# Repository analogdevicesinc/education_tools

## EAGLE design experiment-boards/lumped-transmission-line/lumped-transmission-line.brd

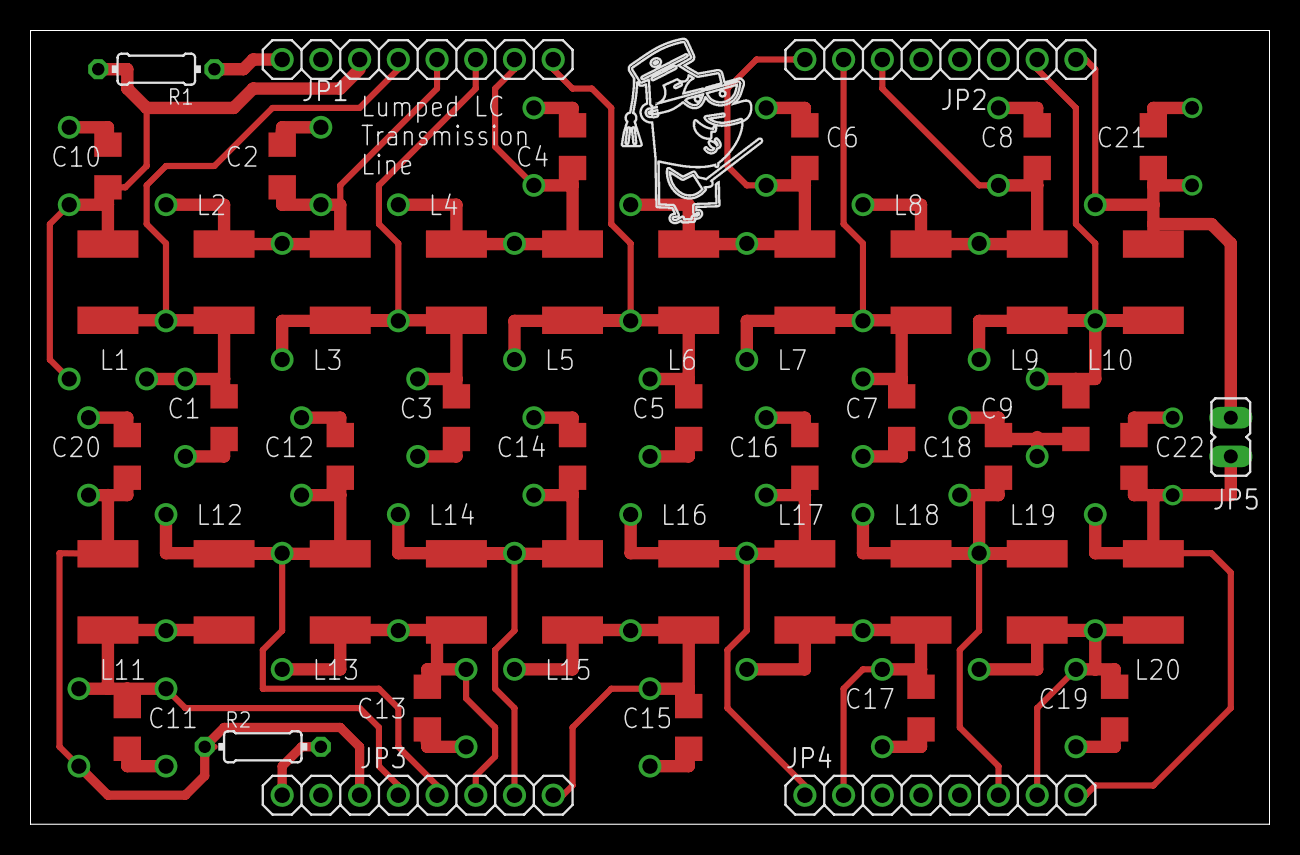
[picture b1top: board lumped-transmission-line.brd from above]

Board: 2 copper layers, 81.3 x 52.1 mm, 50 parts (0 on the bottom side), 25 nets.

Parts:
C1, C2, C3, C4, C5, C6, C7, C8, C9, C10, C11, C12, C13, C14, C15, C16, C17, C18, C19, C20, C21, C22: C1206
JP1, JP2, JP3, JP4: 1X08
JP5: JP1
L1, L2, L3, L4, L5, L6, L7, L8, L9, L10, L11, L12, L13, L14, L15, L16, L17, L18, L19, L20: L5650M
R1, R2: 50; 0204/7
U$1: PROFF

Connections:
GND: C1.2, C2.2, C3.2, C4.2, C5.2, C6.2, C7.2, C8.2, C9.2, C10.2, C11.2, C12.2, C13.2, C14.2, C15.2, C16.2, C17.2, C18.2, C19.2, C20.2, C21.2, C22.2, JP1.2, JP2.4, JP2.5, JP2.6, JP3.2, JP4.3, JP4.4, JP4.5
unnamed: C3.1, JP1.6, L3.2, L4.1
unnamed: C21.1, JP2.8, JP5.1, L10.2
unnamed: C22.1, JP4.8, JP5.2, L20.2
unnamed: C9.1, JP2.7, L9.2, L10.1
unnamed: C19.1, JP4.7, L19.2, L20.1
unnamed: JP1.1, R1.1
unnamed: C15.1, JP3.8, L15.2, L16.1
unnamed: C17.1, JP4.2, L17.2, L18.1
unnamed: C18.1, JP4.6, L18.2, L19.1
unnamed: JP3.1, R2.2
unnamed: C13.1, JP3.6, L13.2, L14.1
unnamed: C11.1, JP3.4, L11.2, L12.1
unnamed: C6.1, JP2.1, L6.2, L7.1
unnamed: C4.1, JP1.7, L4.2, L5.1
unnamed: C2.1, JP1.5, L2.2, L3.1
unnamed: C10.1, JP1.3, L1.1, R1.2
unnamed: C8.1, JP2.3, L8.2, L9.1
unnamed: C20.1, JP3.3, L11.1, R2.1
unnamed: C1.1, JP1.4, L1.2, L2.1
unnamed: C12.1, JP3.5, L12.2, L13.1
unnamed: C14.1, JP3.7, L14.2, L15.1
unnamed: C5.1, JP1.8, L5.2, L6.1
unnamed: C16.1, JP4.1, L16.2, L17.1
unnamed: C7.1, JP2.2, L7.2, L8.1

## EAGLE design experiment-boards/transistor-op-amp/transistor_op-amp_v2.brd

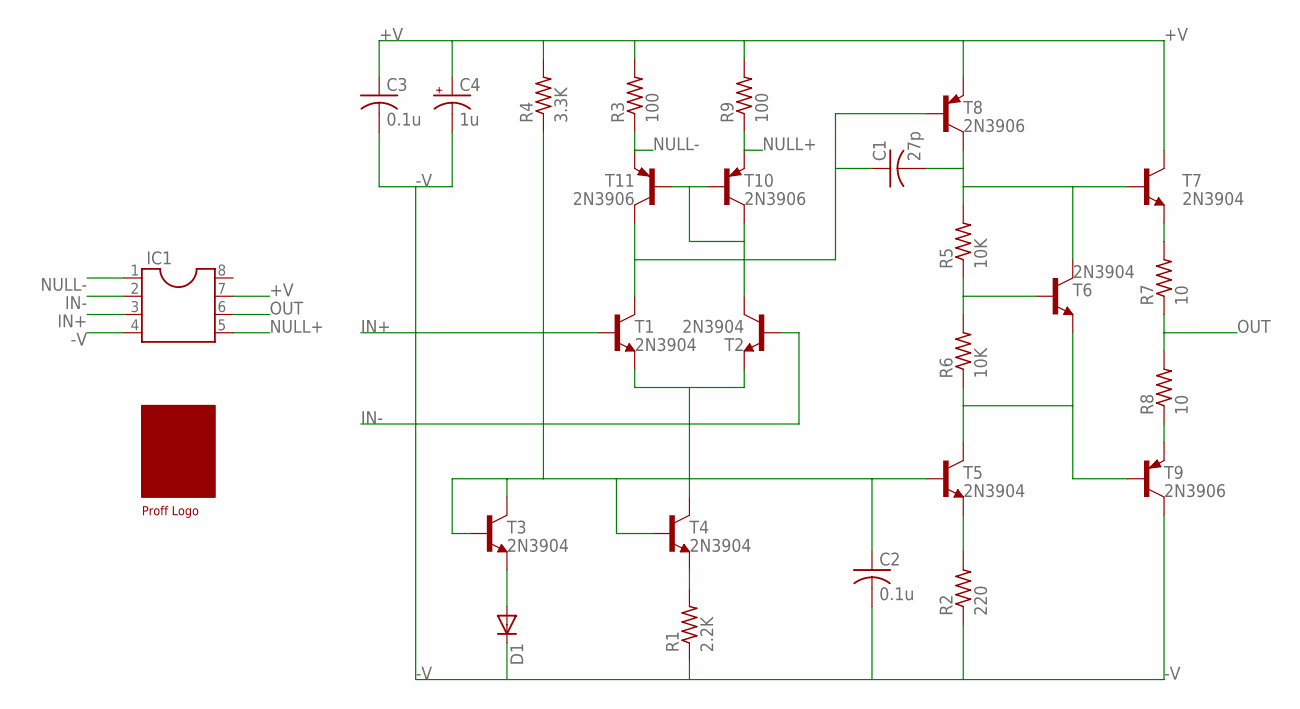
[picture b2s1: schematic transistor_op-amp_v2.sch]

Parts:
C1: 27p; C050-024X044
C2, C3: 0.1u; C050-024X044
C4: 1u; E2,5-5
D1: DIODE-D-7.5; D-7.5
IC1: DIL8S; SOCKET-08
R1: 2.2K; 0207/7
R2: 220; 0207/7
R3, R9: 100; 0207/7
R4: 3.3K; 0207/7
R5, R6: 10K; 0207/7
R7, R8: 10; 0207/7
T1, T2, T3, T4, T5, T6, T7: 2N3904; TO92
T8, T9, T10, T11: 2N3906; TO92
U$1: PROFF

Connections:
+V: C3.1, C4.+, IC1.7, R3.2, R4.2, R9.2, T7.1 (C), T8.3 (E)
-V: C2.2, C3.2, C4.-, D1.C, IC1.4, R1.1, R2.1, T9.1 (C)
IN+: IC1.3, T1.2 (B)
IN-: IC1.2, T2.2 (B)
unnamed: D1.A, T3.3 (E)
unnamed: C2.1, R4.1, T3.1 (C), T3.2 (B), T4.2 (B), T5.2 (B)
unnamed: R1.2, T4.3 (E)
unnamed: R2.2, T5.3 (E)
unnamed: T1.3 (E), T2.3 (E), T4.1 (C)
unnamed: R7.2, T7.3 (E)
unnamed: R6.1, T5.1 (C), T6.3 (E), T9.2 (B)
unnamed: R5.1, R6.2, T6.2 (B)
unnamed: C1.2, R5.2, T6.1 (C), T7.2 (B), T8.1 (C)
unnamed: R8.1, T9.3 (E)
unnamed: C1.1, T1.1 (C), T8.2 (B), T11.1 (C)
unnamed: T2.1 (C), T10.1 (C), T10.2 (B), T11.2 (B)
NULL+: IC1.5, R9.1, T10.3 (E)
NULL-: IC1.1, R3.1, T11.3 (E)
OUT: IC1.6, R7.1, R8.2

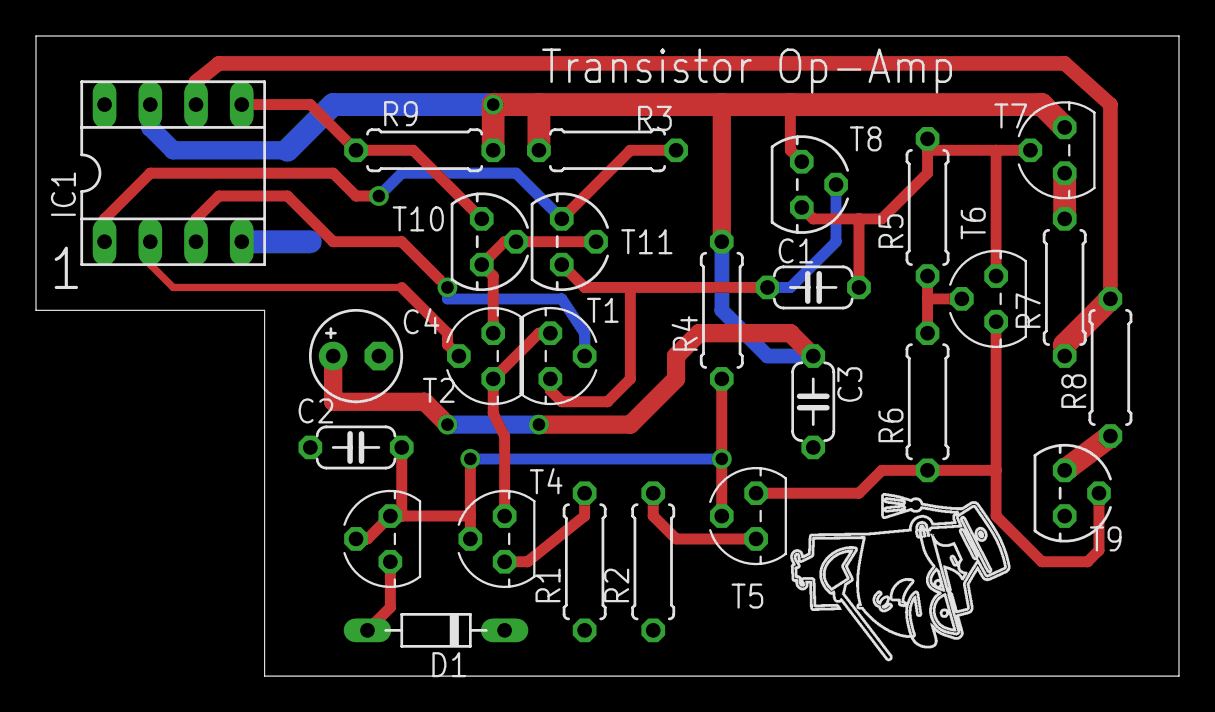
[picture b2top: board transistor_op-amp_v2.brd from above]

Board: 2 copper layers, 63.5 x 35.6 mm, 27 parts (0 on the bottom side), 19 nets.

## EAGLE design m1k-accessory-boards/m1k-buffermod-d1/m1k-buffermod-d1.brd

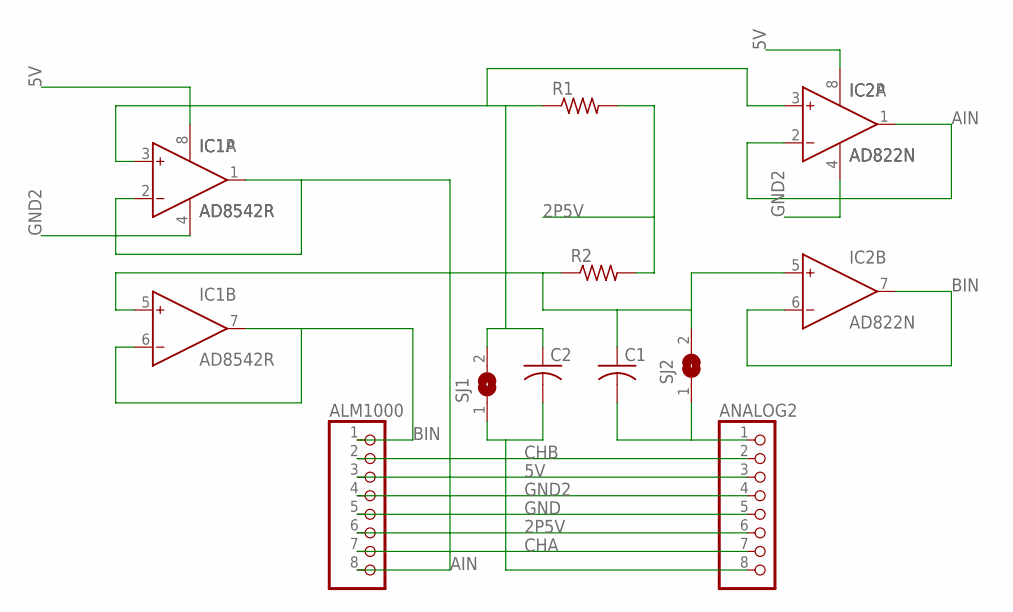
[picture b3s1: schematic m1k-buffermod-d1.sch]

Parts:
ALM1000: PINHD-1X8; 1X08
ANALOG2: PINHD-1X8; 1X08
C1, C2: C-US050-024X044; C050-024X044
IC1: AD8542R; SO8
IC2: AD822N; DIL08
R1, R2: R-US_0204/7; 0204/7
SJ1, SJ2: SJ

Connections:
2P5V: ALM1000.6, ANALOG2.6, R1.2, R2.2
5V: ALM1000.3, ANALOG2.3, IC1.8 (V+), IC2.8 (V+)
AIN: ALM1000.8, IC1.1 (OUT), IC1.2 (IN-), IC2.1 (OUT), IC2.2 (IN-)
BIN: ALM1000.1, IC1.6 (IN-), IC1.7 (OUT), IC2.6 (IN-), IC2.7 (OUT)
CHA: ALM1000.7, ANALOG2.7
CHB: ALM1000.2, ANALOG2.2
GND: ALM1000.5, ANALOG2.5
GND2: ALM1000.4, ANALOG2.4, IC1.4 (V-), IC2.4 (V-)
unnamed: ANALOG2.1, C1.2, SJ2.1
unnamed: ANALOG2.8, C2.2, SJ1.1
unnamed: C2.1, IC1.3 (IN+), IC2.3 (IN+), R1.1, SJ1.2
unnamed: C1.1, IC1.5 (IN+), IC2.5 (IN+), R2.1, SJ2.2

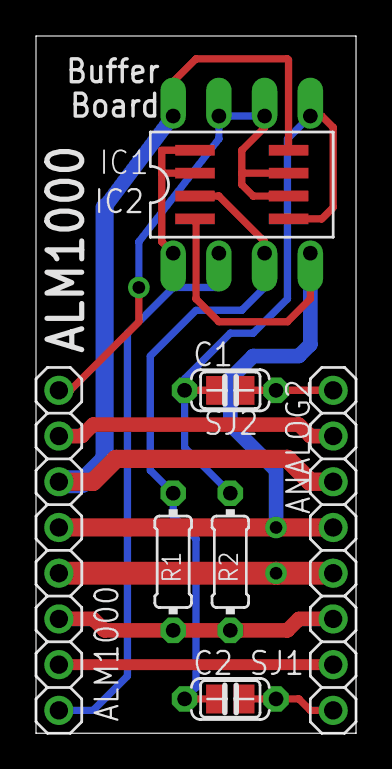
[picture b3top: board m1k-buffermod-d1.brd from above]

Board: 2 copper layers, 17.8 x 38.7 mm, 10 parts (0 on the bottom side), 12 nets.

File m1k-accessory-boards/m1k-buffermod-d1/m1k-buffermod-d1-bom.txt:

Partlist exported from m1k-buffermod-d1.sch at 4/23/2020 8:39 AM

Part    Value   Device          Package      Description                                            MF                 MPN
ALM1000         PINHD-1X8       1X08         PIN HEADER                                                                                                   
ANALOG2         PINHD-1X8       1X08         PIN HEADER                                                                                                   
C1      Various C-US050-024X044 C050-024X044 CAPACITOR                                                                                   
C2      Various C-US050-024X044 C050-024X044 CAPACITOR                                                                                   
IC1     AD8542R AD8542R         SO8          General-Purpose CMOS Rail-to-Rail Amplifiers           Analog Devices AD8542ARZ  
IC2     AD822N  AD822N          DIL08        Single-Supply, Rail-to-Rail Low Power FET-Input Op Amp                           
R1      Various R-US_0204/7     0204/7       RESISTOR                                                                                    
R2      Various R-US_0204/7     0204/7       RESISTOR

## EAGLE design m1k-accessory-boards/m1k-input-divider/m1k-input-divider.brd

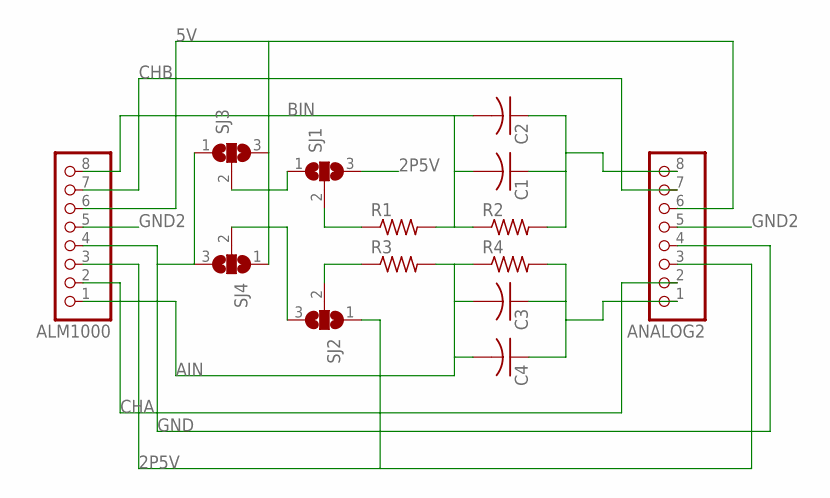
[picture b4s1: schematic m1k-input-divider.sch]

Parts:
ALM1000: PINHD-1X8; 1X08
ANALOG2: PINHD-1X8; 1X08
C1, C2, C3, C4: C-US050-024X044; C050-024X044
R1, R2, R3, R4: R-US_0204/7; 0204/7
SJ1, SJ2, SJ3, SJ4: SJ2W; SJ_2

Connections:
2P5V: ALM1000.3, ANALOG2.3, SJ1.3, SJ2.1
5V: ALM1000.6, ANALOG2.6, SJ3.3, SJ4.1
AIN: ALM1000.1, C3.2, C4.2, R3.2, R4.1
BIN: ALM1000.8, C1.2, C2.2, R1.2, R2.1
CHA: ALM1000.2, ANALOG2.2
CHB: ALM1000.7, ANALOG2.7
GND: ALM1000.4, ANALOG2.4, SJ3.1, SJ4.3
GND2: ALM1000.5, ANALOG2.5
unnamed: SJ1.1, SJ3.2
unnamed: SJ2.3, SJ4.2
unnamed: ANALOG2.1, C3.1, C4.1, R4.2
unnamed: R1.1, SJ1.2
unnamed: R3.1, SJ2.2
unnamed: ANALOG2.8, C1.1, C2.1, R2.2

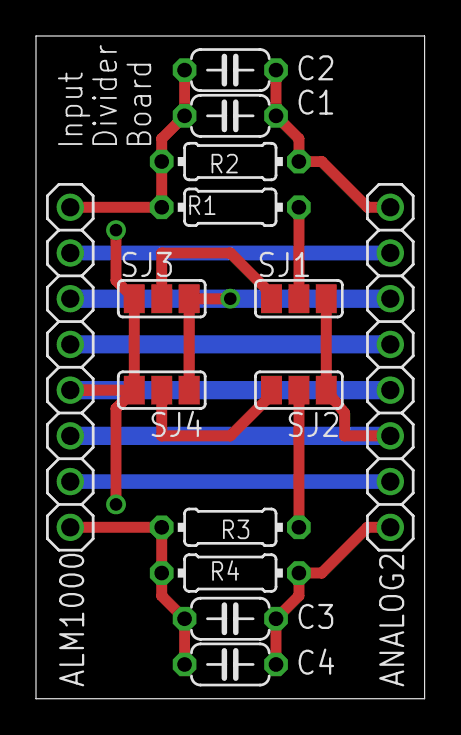
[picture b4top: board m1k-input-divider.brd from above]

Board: 2 copper layers, 21.6 x 36.8 mm, 14 parts (0 on the bottom side), 14 nets.

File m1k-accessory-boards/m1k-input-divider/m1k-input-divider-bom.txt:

Partlist exported from m1k-input-divider.sch at 4/23/2020 8:45 AM

Part    Value   Device          Package      Description                
ALM1000         PINHD-1X8       1X08         PIN HEADER                 
ANALOG2         PINHD-1X8       1X08         PIN HEADER                 
C1      Various C-US050-024X044 C050-024X044 CAPACITOR 
C2      Various C-US050-024X044 C050-024X044 CAPACITOR 
C3      Various C-US050-024X044 C050-024X044 CAPACITOR 
C4      Various C-US050-024X044 C050-024X044 CAPACITOR 
R1      Various R-US_0204/7     0204/7       RESISTOR  
R2      Various R-US_0204/7     0204/7       RESISTOR  
R3      Various R-US_0204/7     0204/7       RESISTOR  
R4      Various R-US_0204/7     0204/7       RESISTOR

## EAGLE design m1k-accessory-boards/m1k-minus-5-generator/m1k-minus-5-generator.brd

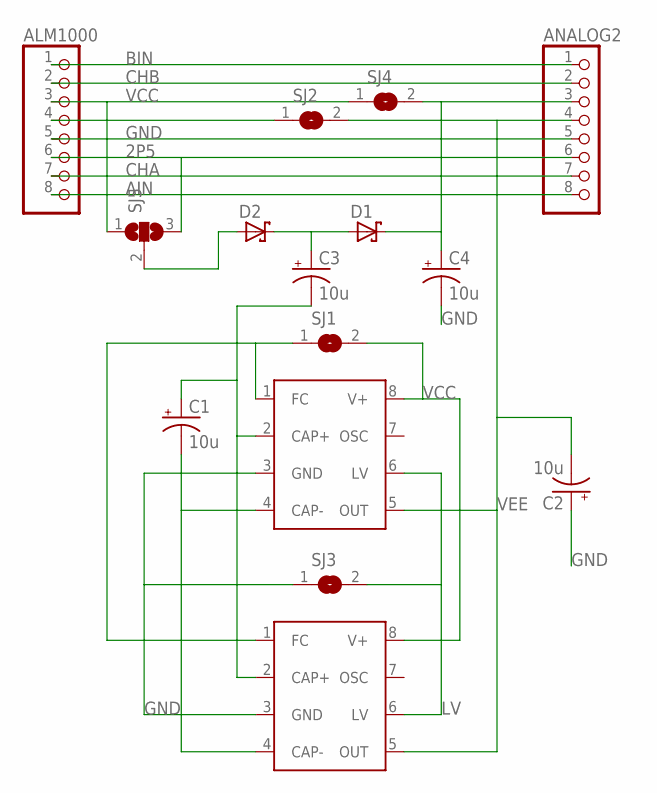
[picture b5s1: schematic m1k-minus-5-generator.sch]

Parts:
ALM1000: PINHD-1X8; 1X08
ANALOG2: PINHD-1X8; 1X08
C1, C2, C3, C4: 10u; E2,5-6E
D1, D2: SCHOTTKY-DIODEDO35-7; DO35-7
SJ1, SJ2, SJ3, SJ4: SJ
SJ5: SJ2W; SJ_2
U1: ADM660; SO8
U2: ADM660DIP; DIL8

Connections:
2P5: ALM1000.6, ANALOG2.6, SJ5.3
AIN: ALM1000.8, ANALOG2.8
BIN: ALM1000.1, ANALOG2.1
CHA: ALM1000.7, ANALOG2.7
CHB: ALM1000.2, ANALOG2.2
GND: ALM1000.5, ANALOG2.5, C2.+, C4.-, SJ3.1, U1.3 (GND), U2.3 (GND)
LV: SJ3.2, U1.6 (LV), U2.6 (LV)
unnamed: ALM1000.4, SJ2.1
unnamed: ANALOG2.3, C4.+, D1.C, SJ4.2
unnamed: C3.+, D1.A, D2.C
unnamed: D2.A, SJ5.2
unnamed: C1.+, C3.-, U1.2 (CAP+), U2.2 (CAP+)
unnamed: C1.-, U1.4 (CAP-), U2.4 (CAP-)
unnamed: SJ1.1, U1.1 (FC), U2.1 (FC)
VCC: ALM1000.3, SJ1.2, SJ4.1, SJ5.1, U1.8 (V+), U2.8 (V+)
VEE: ANALOG2.4, C2.-, SJ2.2, U1.5 (OUT), U2.5 (OUT)

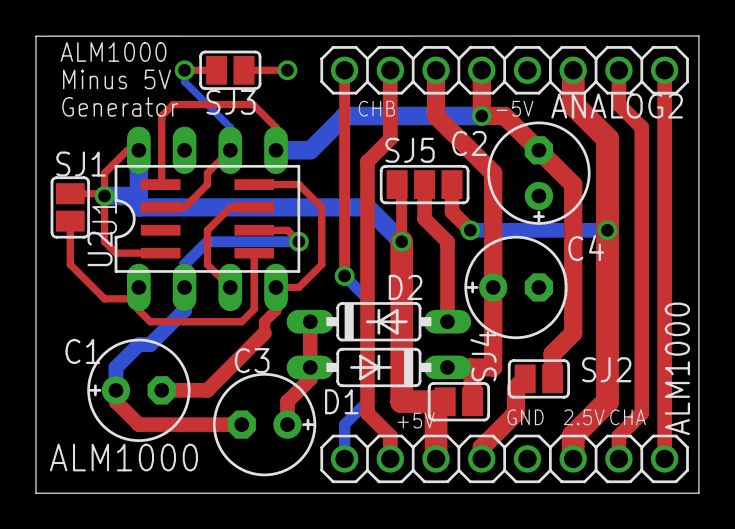
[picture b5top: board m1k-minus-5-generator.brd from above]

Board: 2 copper layers, 36.8 x 25.4 mm, 15 parts (0 on the bottom side), 16 nets.

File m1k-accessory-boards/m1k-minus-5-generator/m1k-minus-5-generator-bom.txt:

Partlist exported from m1k-minus-5-generator.sch at 4/23/2020 8:37 AM

Part    Value     Device               Package Description                          
ALM1000           PINHD-1X8            1X08    PIN HEADER                           
ANALOG2           PINHD-1X8            1X08    PIN HEADER                           
C1      10u       CPOL-USE2,5-6E       E2,5-6E POLARIZED CAPACITOR, American symbol 
C2      10u       CPOL-USE2,5-6E       E2,5-6E POLARIZED CAPACITOR, American symbol 
C3      10u       CPOL-USE2,5-6E       E2,5-6E POLARIZED CAPACITOR, American symbol 
C4      10u       CPOL-USE2,5-6E       E2,5-6E POLARIZED CAPACITOR, American symbol 
D1                SCHOTTKY-DIODEDO35-7 DO35-7  Schottky Diode  
D2                SCHOTTKY-DIODEDO35-7 DO35-7  Schottky Diode  
U1      ADM660    ADM660               SO8     CMOS Switched-Capacitor Voltage Converter 
U1      LT1054    LT1054               SO8     Switched-Capacitor Voltage Converter with Regulator
U2      ADM660DIP ADM660DIP            DIL8    CMOS Switched-Capacitor Voltage Converter 
U2      LT1054DIP LT1054DIP            DIL8    Switched-Capacitor Voltage Converter with Regulator

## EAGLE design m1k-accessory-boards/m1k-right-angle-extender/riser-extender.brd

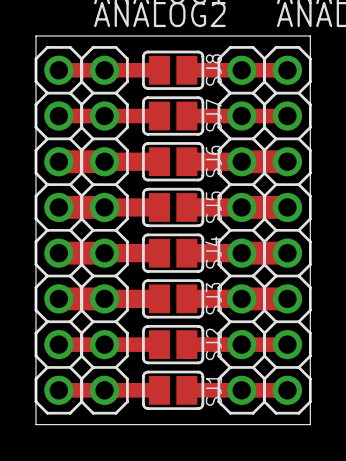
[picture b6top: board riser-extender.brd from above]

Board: 2 copper layers, 15.2 x 21.6 mm, 12 parts (0 on the bottom side), 16 nets.

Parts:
ANALOG1, ANALOG2, ANALOG3, ANALOG4: 1X08
SJ1, SJ2, SJ3, SJ4, SJ5, SJ6, SJ7, SJ8: SJ

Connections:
unnamed: ANALOG1.1, ANALOG2.1, SJ8.2
unnamed: ANALOG1.2, ANALOG2.2, SJ7.2
unnamed: ANALOG1.3, ANALOG2.3, SJ6.2
unnamed: ANALOG1.4, ANALOG2.4, SJ5.2
unnamed: ANALOG1.5, ANALOG2.5, SJ4.2
unnamed: ANALOG1.6, ANALOG2.6, SJ3.2
unnamed: ANALOG1.7, ANALOG2.7, SJ2.2
unnamed: ANALOG1.8, ANALOG2.8, SJ1.2
unnamed: ANALOG3.5, ANALOG4.5, SJ4.1
unnamed: ANALOG3.6, ANALOG4.6, SJ3.1
unnamed: ANALOG3.7, ANALOG4.7, SJ2.1
unnamed: ANALOG3.8, ANALOG4.8, SJ1.1
unnamed: ANALOG3.4, ANALOG4.4, SJ5.1
unnamed: ANALOG3.3, ANALOG4.3, SJ6.1
unnamed: ANALOG3.2, ANALOG4.2, SJ7.1
unnamed: ANALOG3.1, ANALOG4.1, SJ8.1

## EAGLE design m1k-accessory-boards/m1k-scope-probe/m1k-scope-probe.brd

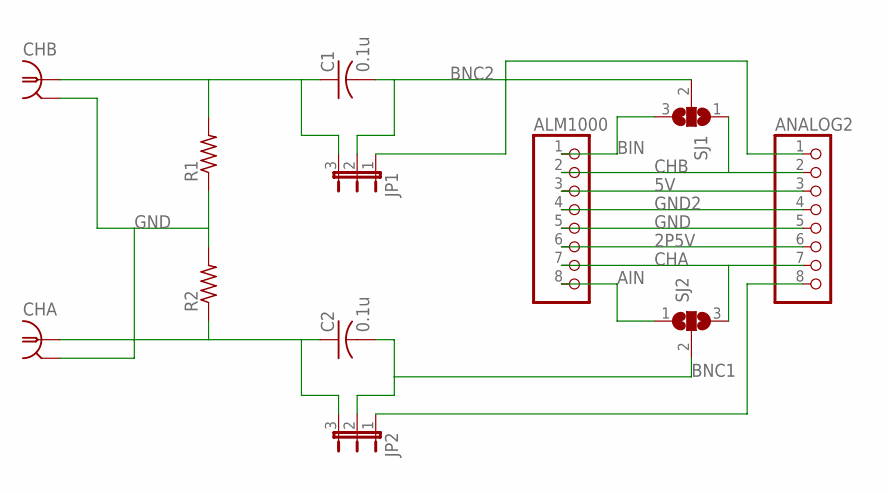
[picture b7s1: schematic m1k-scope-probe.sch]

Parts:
ALM1000: PINHD-1X8; 1X08
ANALOG2: PINHD-1X8; 1X08
C1, C2: 0.1u; C050-024X044
CHA: 227161-8; AMP_227161
CHB: 227161-8; AMP_227161
JP1, JP2: JP2E; JP2
R1, R2: R-US_0204/7; 0204/7
SJ1, SJ2: SJ2W; SJ_2

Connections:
2P5V: ALM1000.6, ANALOG2.6
5V: ALM1000.3, ANALOG2.3
AIN: ALM1000.8, SJ2.1
BIN: ALM1000.1, SJ1.3
BNC1: C2.2, JP2.2, SJ2.2
BNC2: C1.2, JP1.2, SJ1.2
CHA: ALM1000.7, ANALOG2.7, SJ2.3
CHB: ALM1000.2, ANALOG2.2, SJ1.1
GND: ALM1000.5, ANALOG2.5, CHA.2 (GND), CHB.2 (GND), R1.1, R2.2
GND2: ALM1000.4, ANALOG2.4
unnamed: ANALOG2.8, JP2.1
unnamed: C1.1, CHB.1, JP1.3, R1.2
unnamed: ANALOG2.1, JP1.1
unnamed: C2.1, CHA.1, JP2.3, R2.1

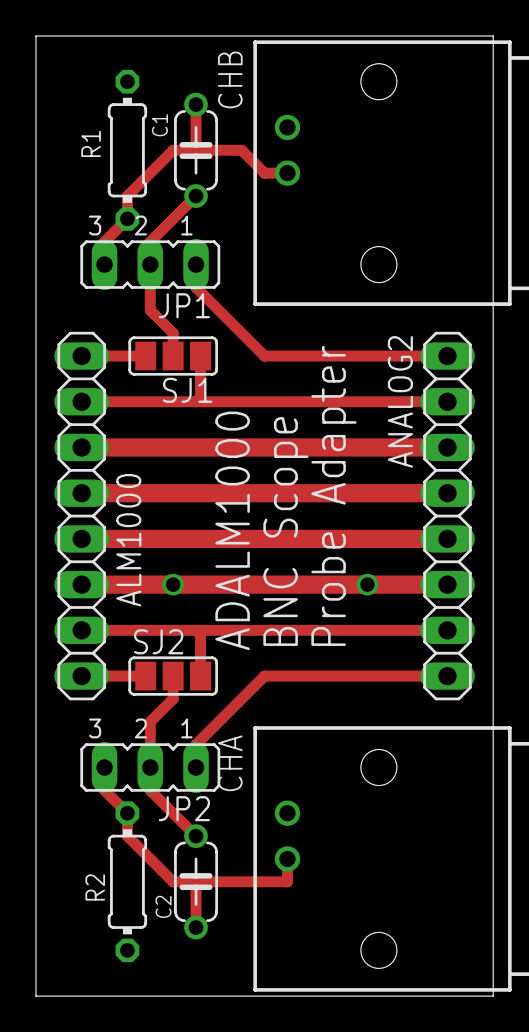
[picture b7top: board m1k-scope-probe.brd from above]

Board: 2 copper layers, 25.4 x 53.3 mm, 12 parts (0 on the bottom side), 14 nets.

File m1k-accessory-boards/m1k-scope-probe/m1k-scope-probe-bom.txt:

Partlist exported from m1k-scope-probe.sch at 4/23/2020 8:50 AM

Part    Value   Device          Package      Description                          MF MPN 
ALM1000         PINHD-1X8       1X08         8 PIN Single row HEADER                                                      
ANALOG2         PINHD-1X8       1X08         6 PIN Single row HEADER                                                      
C1      0.1u    C-US050-024X044 C050-024X044 CAPACITOR                                      
C2      0.1u    C-US050-024X044 C050-024X044 CAPACITOR                                      
CHA             227161-8        AMP_227161   JACK,  RIGHT ANGLE, 50 OHM, PCB, BNC          
CHB             227161-8        AMP_227161   JACK,  RIGHT ANGLE, 50 OHM, PCB, BNC          
JP1             JP2E            JP2          3 pin JUMPER                                                          
JP2             JP2E            JP2          3 pin JUMPER                                                          
R1      Various R-US_0204/7     0204/7       RESISTOR                                       
R2      Various R-US_0204/7     0204/7       RESISTOR
